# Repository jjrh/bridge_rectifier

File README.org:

* Bridge rectifier
  - using: MUR860G diodes

* datasheets
  https://www.fairchildsemi.com/datasheets/RU/RURP860.pdf

#+START_IMAGES:

#+END_IMAGES:

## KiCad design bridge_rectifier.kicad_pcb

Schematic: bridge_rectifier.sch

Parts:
C1: C
C2, C3, C4, C5: C_Small; C_Disc_D7.5_P5
D1: D
D2: LED
D3, D4, D5, D6: MUR860G; Diode_TO-220_Vertical
P1: AC_INPUT
P2: OUTPUT
P3, P4, P5, P6: MOUNTING_HOLES
R1: R

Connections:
/HOT: C1.2, C2.1, C3.1, D3.1 (K), D4.2 (A), P1.1
/Netural: C4.1, C5.2, D5.1 (K), D6.2 (A), P1.2, R1.2
/V+: C3.2, C5.1, D4.1 (K), D6.1 (K), P2.1
/V-: C2.2, C4.2, D3.2 (A), D5.2 (A), P2.2
unnamed: C1.1, D1.1 (K), D2.2 (A)
unnamed: D1.2 (A), D2.1 (K), R1.1

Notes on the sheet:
LIVE POWER INDICATION
120V INPUT
RECTIFED OUTPUT

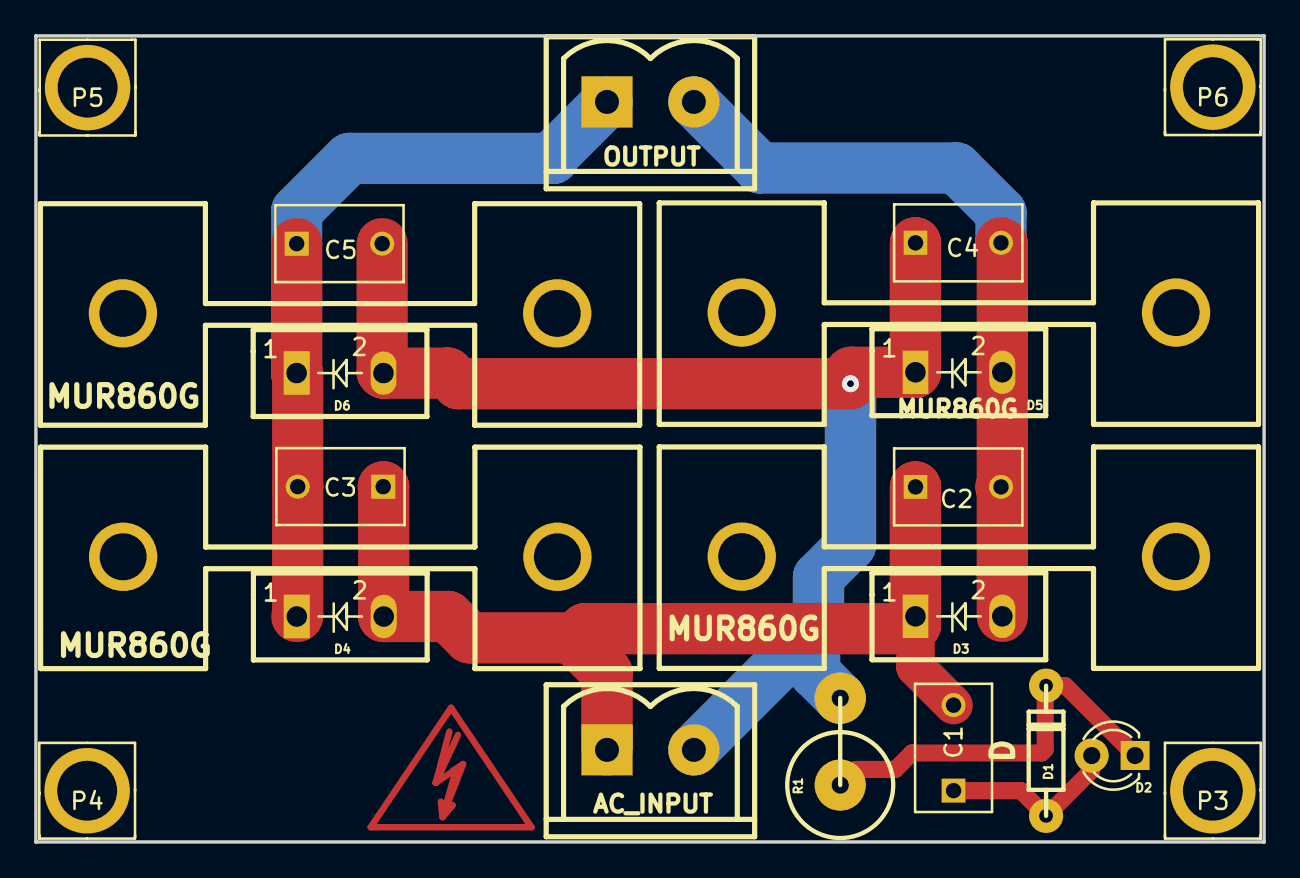
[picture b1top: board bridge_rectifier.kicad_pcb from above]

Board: 2 copper layers, 71.8 x 47.1 mm, 18 parts (0 on the bottom side), 6 nets.

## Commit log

2016-01-08 initialized repo
2016-01-09 updated license
2016-01-10 trying to route the board within sqrt(2500)
2016-01-16 routed final
2016-01-16 added highvoltage symbol
2016-01-16 removed template stuff from readme
